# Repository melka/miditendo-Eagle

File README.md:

# miditendo

Eagle project for the miditendo, a USB midi controller in a SNES gamepad, using [v-usb](http://www.obdev.at/products/vusb/index.html)

Included is a small board for programming ATTiny45/85 via ICSP without soldering a header (piggyback).

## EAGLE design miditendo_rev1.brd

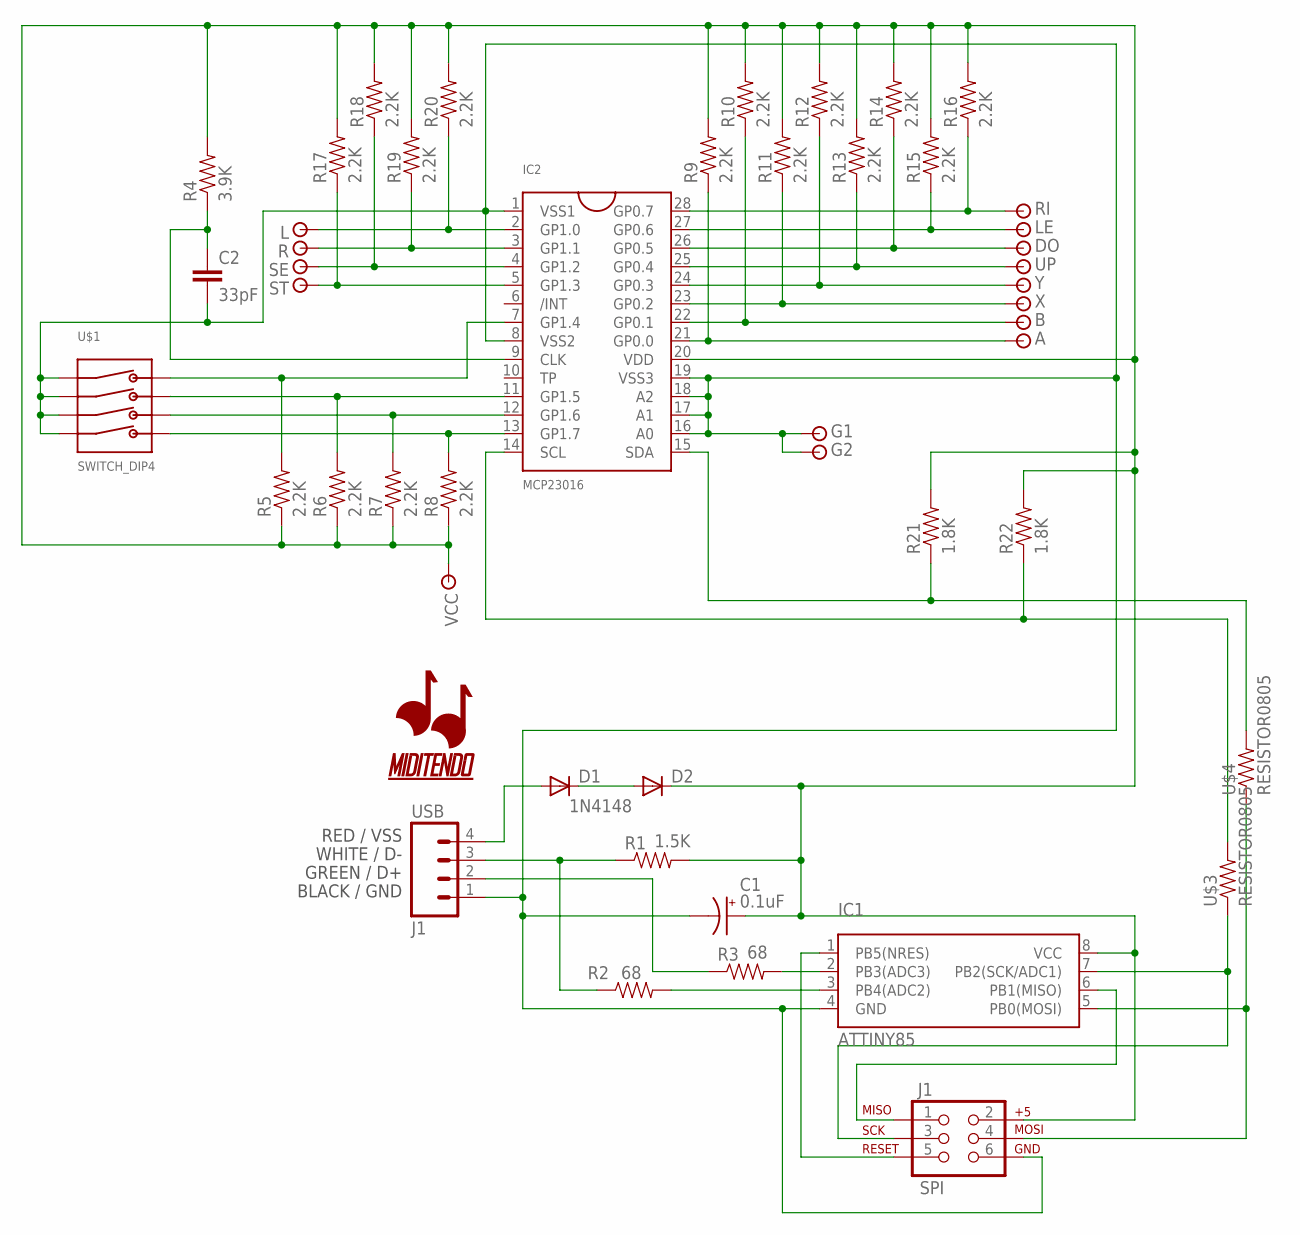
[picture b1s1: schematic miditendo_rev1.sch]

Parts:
A: WIRE_JOINT; THSOLDERPOINT
B: WIRE_JOINT; THSOLDERPOINT
C1: 0.1uF; POLCAP_2.54
C2: 33pF; 0805
D1: LL4148SOD-80C; SOD-80C
D2: 1N4148; SOD-80C
DO: WIRE_JOINT; THSOLDERPOINT
G1, G2: WIRE_JOINT; THSOLDERPOINT
IC1: ATTINY85; SOIC8-EIAJ
IC2: MCP23016; SOIC28
J1: SPI; 2X3-NS
L: WIRE_JOINT; THSOLDERPOINT
LE: WIRE_JOINT; THSOLDERPOINT
R: WIRE_JOINT; THSOLDERPOINT
R1: 1.5K; 0805
R2, R3: 68; 0805
R4: 3.9K; 0805
R5, R6, R7, R8, R9, R10, R11, R12, R13, R14, R15, R16, R17, R18, R19, R20: 2.2K; 0805
R21, R22: 1.8K; 0805
RI: WIRE_JOINT; THSOLDERPOINT
SE: WIRE_JOINT; THSOLDERPOINT
ST: WIRE_JOINT; THSOLDERPOINT
U$1: SWITCH_DIP4; SWITCH_4DIP
U$2: MIDITENDO
U$3, U$4: RESISTOR0805; 0805
UP: WIRE_JOINT; THSOLDERPOINT
USB: J1; 1X04_LONGPADS
VCC: WIRE_JOINT; THSOLDERPOINT
X: WIRE_JOINT; THSOLDERPOINT
Y: WIRE_JOINT; THSOLDERPOINT

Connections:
GND: C1.N (-), C2.2, G1.P$1, G2.P$1, IC1.4 (GND), IC2.1 (VSS1), IC2.8 (VSS2), IC2.16 (A0), IC2.17 (A1), IC2.18 (A2), IC2.19 (VSS3), J1.6, U$1.P$1, U$1.P$2, U$1.P$3, U$1.P$4, USB.1
unnamed: D1.PA (A), USB.4
unnamed: D1.PC (C), D2.PA (A)
unnamed: IC2.2 (GP1.0), L.P$1, R20.1
unnamed: IC2.15 (SDA), R21.1, U$4.2
unnamed: R3.1, USB.2
unnamed: IC2.14 (SCL), R22.1, U$3.2
unnamed: IC1.2 (PB3(ADC3)), R3.2
unnamed: IC1.3 (PB4(ADC2)), R2.2
unnamed: IC2.3 (GP1.1), R.P$1, R19.1
unnamed: R1.1, R2.1, USB.3
unnamed: IC2.4 (GP1.2), R18.1, SE.P$1
unnamed: IC2.5 (GP1.3), R17.1, ST.P$1
unnamed: IC2.28 (GP0.7), R16.1, RI.P$1
unnamed: IC2.27 (GP0.6), LE.P$1, R15.1
unnamed: DO.P$1, IC2.26 (GP0.5), R14.1
unnamed: IC2.25 (GP0.4), R13.1, UP.P$1
unnamed: IC2.24 (GP0.3), R12.1, Y.P$1
unnamed: IC2.23 (GP0.2), R11.1, X.P$1
unnamed: B.P$1, IC2.22 (GP0.1), R10.1
unnamed: A.P$1, IC2.21 (GP0.0), R9.1
unnamed: C2.1, IC2.9 (CLK), R4.1
unnamed: IC1.6 (PB1(MISO)), J1.1
unnamed: IC1.1 (PB5(NRES)), J1.5
unnamed: IC1.7 (PB2(SCK/ADC1)), J1.3, U$3.1
unnamed: IC1.5 (PB0(MOSI)), J1.4, U$4.1
unnamed: IC2.13 (GP1.7), R8.2, U$1.P$5
unnamed: IC2.12 (GP1.6), R7.2, U$1.P$6
unnamed: IC2.11 (GP1.5), R6.2, U$1.P$7
unnamed: IC2.7 (GP1.4), R5.2, U$1.P$8
VDD: C1.P (+), D2.PC (C), IC1.8 (VCC), IC2.20 (VDD), J1.2, R1.2, R4.2, R5.1, R6.1, R7.1, R8.1, R9.2, R10.2, R11.2, R12.2, R13.2, R14.2, R15.2, R16.2, R17.2, R18.2, R19.2, R20.2, R21.2, R22.2, VCC.P$1

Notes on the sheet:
RED / VSS
WHITE / D-
GREEN / D+
BLACK / GND

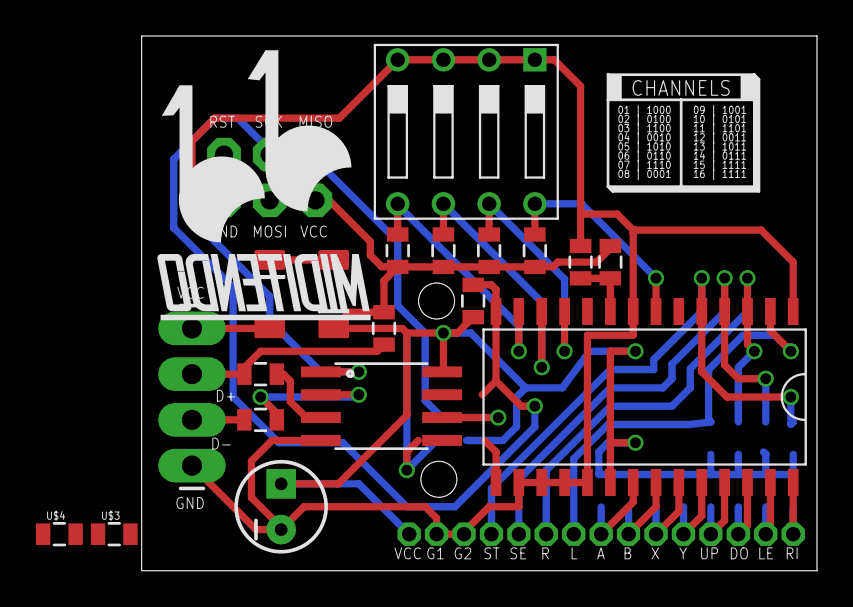
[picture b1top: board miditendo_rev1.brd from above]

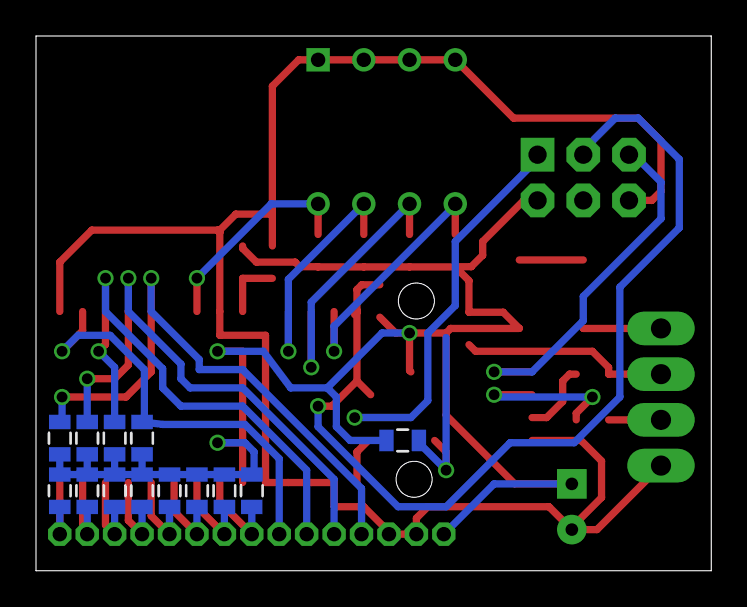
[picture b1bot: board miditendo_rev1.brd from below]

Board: 2 copper layers, 37.5 x 29.7 mm, 49 parts (14 on the bottom side), 31 nets.

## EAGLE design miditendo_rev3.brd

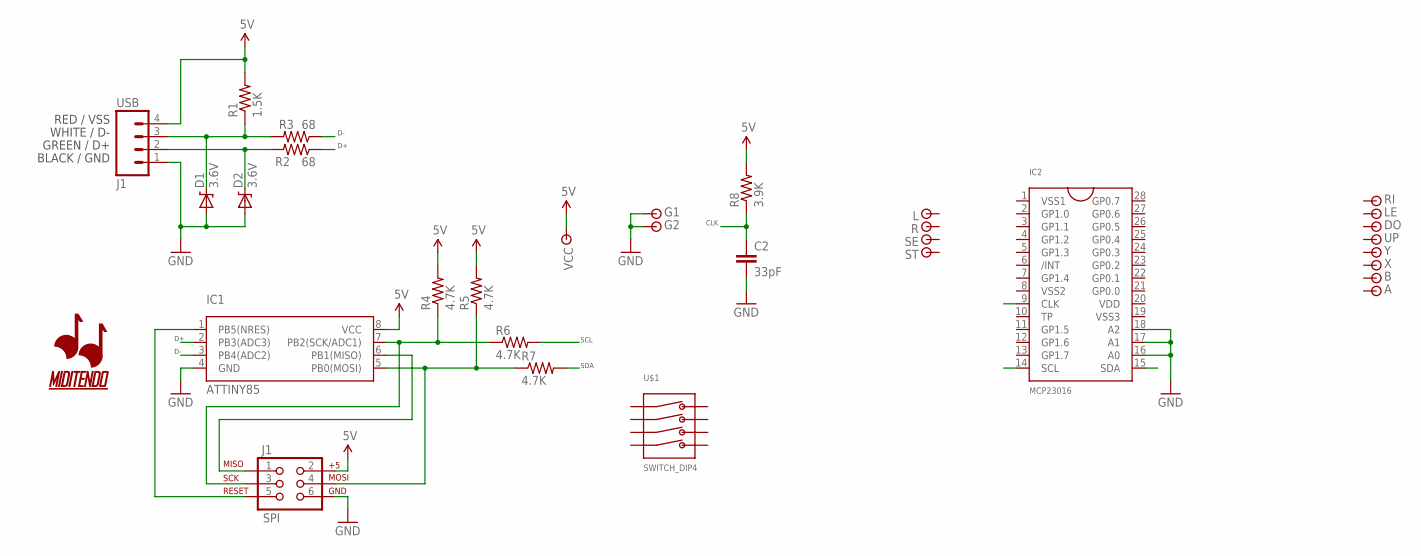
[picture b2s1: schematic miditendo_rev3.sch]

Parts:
A: WIRE_JOINT; THSOLDERPOINT
B: WIRE_JOINT; THSOLDERPOINT
C2: 33pF; 0805
D1, D2: 3.6V; DIODE-ZENER
DO: WIRE_JOINT; THSOLDERPOINT
G1, G2: WIRE_JOINT; THSOLDERPOINT
IC1: ATTINY85; SOIC8-EIAJ
IC2: MCP23016; SOIC28
J1: SPI; 2X3-NS
L: WIRE_JOINT; THSOLDERPOINT
LE: WIRE_JOINT; THSOLDERPOINT
R: WIRE_JOINT; THSOLDERPOINT
R1: 1.5K; 0805
R2, R3: 68; 0805
R4, R5, R6, R7: 4.7K; 0805
R8: 3.9K; 0805
RI: WIRE_JOINT; THSOLDERPOINT
SE: WIRE_JOINT; THSOLDERPOINT
ST: WIRE_JOINT; THSOLDERPOINT
U$1: SWITCH_DIP4; SWITCH_4DIP
U$2: MIDITENDO
UP: WIRE_JOINT; THSOLDERPOINT
USB: J1; 1X04_LONGPADS
VCC: WIRE_JOINT; THSOLDERPOINT
X: WIRE_JOINT; THSOLDERPOINT
Y: WIRE_JOINT; THSOLDERPOINT

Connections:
5V: IC1.8 (VCC), J1.2, R1.2, R4.2, R5.2, R8.2, USB.4, VCC.P$1
CLK: C2.1, IC2.9 (CLK), R8.1
D+: IC1.2 (PB3(ADC3)), R2.1
D-: IC1.3 (PB4(ADC2)), R3.1
GND: C2.2, D1.P$2 (A), D2.P$2 (A), G1.P$1, G2.P$1, IC1.4 (GND), IC2.16 (A0), IC2.17 (A1), IC2.18 (A2), J1.6, USB.1
MOSI: IC1.5 (PB0(MOSI)), J1.4, R5.1, R7.1
unnamed: D1.P$1 (C), R1.1, R3.2, USB.3
unnamed: IC1.1 (PB5(NRES)), J1.5
unnamed: D2.P$1 (C), R2.2, USB.2
unnamed: IC1.6 (PB1(MISO)), J1.1
SCK: IC1.7 (PB2(SCK/ADC1)), J1.3, R4.1, R6.1
SCL: IC2.14 (SCL), R6.2
SDA: IC2.15 (SDA), R7.2
VDD: IC2.20 (VDD)
VSS1: IC2.1 (VSS1)
VSS2: IC2.8 (VSS2)
VSS3: IC2.19 (VSS3)

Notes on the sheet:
RED / VSS
WHITE / D-
GREEN / D+
BLACK / GND
SCL
SDA
CLK

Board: 2 copper layers, 32 parts (0 on the bottom side), 13 nets, no tracks yet.

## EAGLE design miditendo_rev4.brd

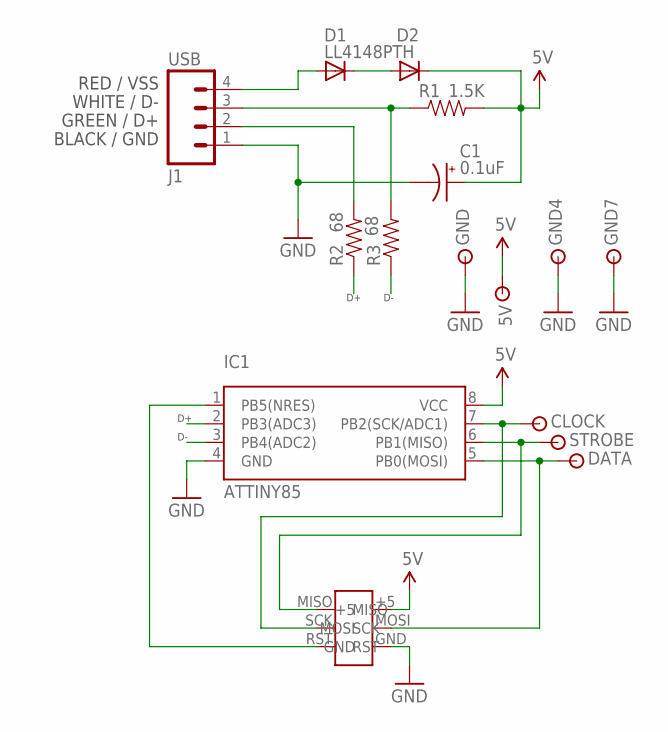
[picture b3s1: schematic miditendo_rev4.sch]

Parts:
5V: WIRE_JOINT; THSOLDERPOINT
C1: 0.1uF; POLCAP_2.54
CLOCK: WIRE_JOINT; THSOLDERPOINT
D1, D2: LL4148PTH; 1N4148-PTH
DATA: WIRE_JOINT; THSOLDERPOINT
GND, GND4, GND7: WIRE_JOINT; THSOLDERPOINT
IC1: ATTINY85; DIP8
R1: 1.5K; 0805
R2, R3: 68; 0805
STROBE: WIRE_JOINT; THSOLDERPOINT
U$1: ICSPSMD; ICSP_SMD
USB: J1; 1X04-SMD

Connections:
5V: 5V.P$1, C1.P (+), D2.C, IC1.8 (VCC), R1.2, U$1.+5
D+: IC1.2 (PB3(ADC3)), R2.1
D-: IC1.3 (PB4(ADC2)), R3.1
GND: C1.N (-), GND.P$1, GND4.P$1, GND7.P$1, IC1.4 (GND), U$1.GND, USB.1
MOSI: DATA.P$1, IC1.5 (PB0(MOSI)), U$1.MOSI
unnamed: D1.A, USB.4
unnamed: D1.C, D2.A
unnamed: IC1.6 (PB1(MISO)), STROBE.P$1, U$1.MISO
unnamed: CLOCK.P$1, IC1.7 (PB2(SCK/ADC1)), U$1.SCK
unnamed: R2.2, USB.2
unnamed: R1.1, R3.2, USB.3
unnamed: IC1.1 (PB5(NRES)), U$1.RST

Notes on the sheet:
RED / VSS
WHITE / D-
GREEN / D+
BLACK / GND

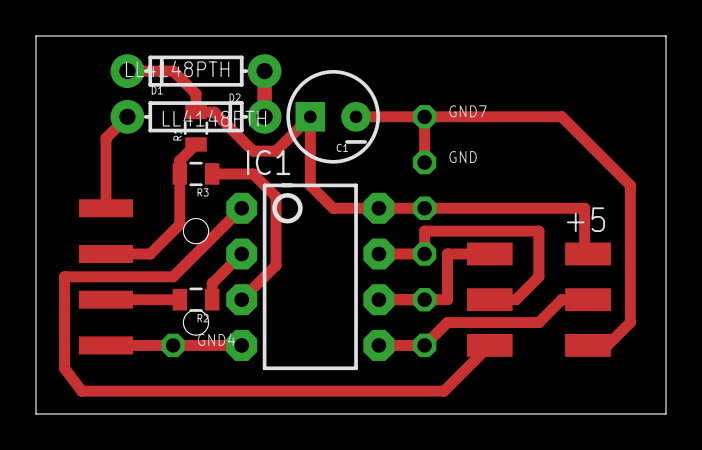
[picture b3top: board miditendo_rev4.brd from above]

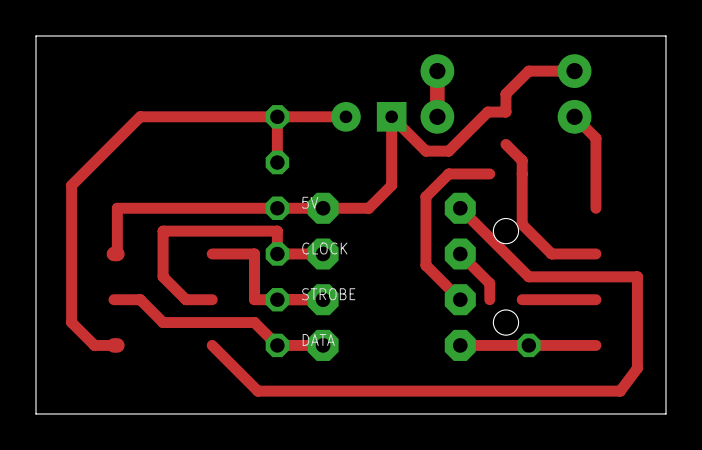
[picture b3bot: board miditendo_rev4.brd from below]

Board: 2 copper layers, 35.0 x 21.0 mm, 16 parts (4 on the bottom side), 12 nets.

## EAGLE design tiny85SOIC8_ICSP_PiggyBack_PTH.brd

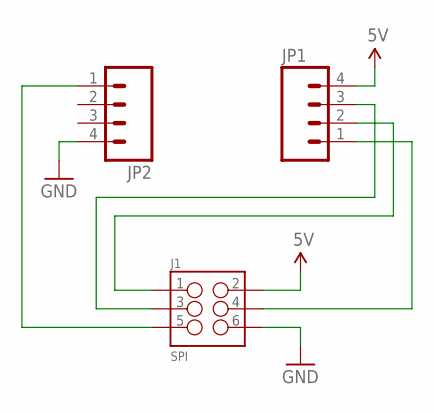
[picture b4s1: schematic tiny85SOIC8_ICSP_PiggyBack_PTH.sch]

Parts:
J1: SPI; 2X3-NS
JP1, JP2: M041.27MM; 1X04-1.27MM

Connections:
5V: J1.2, JP1.4
GND: J1.6, JP2.4
MISO: J1.1, JP1.2
MOSI: J1.4, JP1.1
RST: J1.5, JP2.1
SCK: J1.3, JP1.3

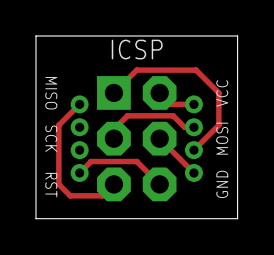
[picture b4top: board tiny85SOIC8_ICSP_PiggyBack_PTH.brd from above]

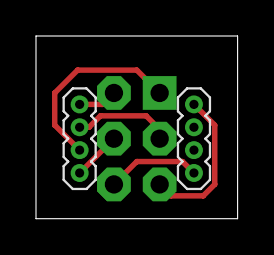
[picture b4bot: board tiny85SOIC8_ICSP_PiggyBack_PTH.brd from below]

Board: 4 copper layers, 11.2 x 10.2 mm, 3 parts (2 on the bottom side), 6 nets.

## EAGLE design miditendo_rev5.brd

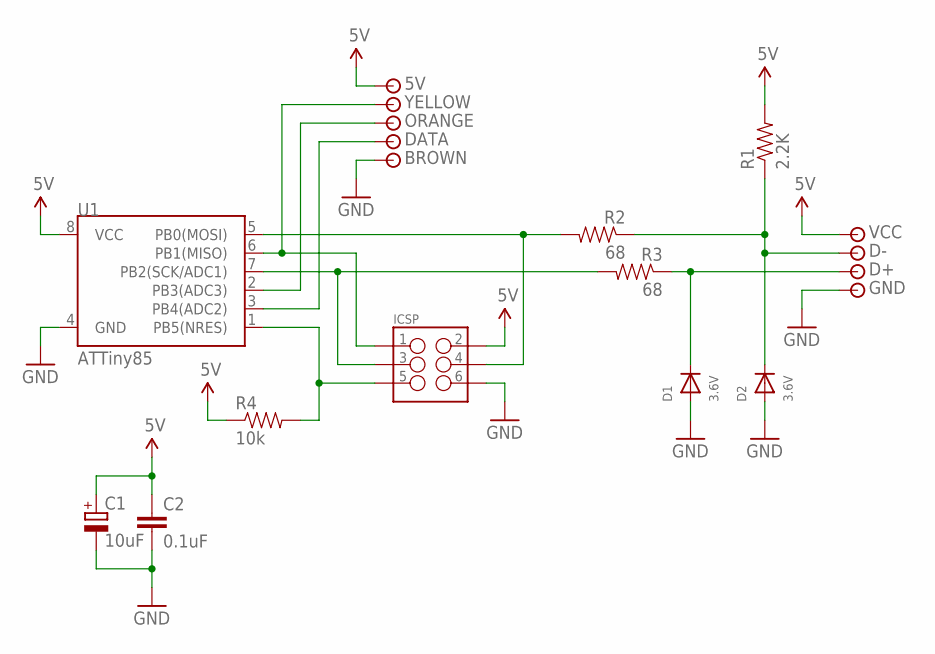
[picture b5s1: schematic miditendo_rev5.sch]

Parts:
5V: WIRE_JOINT; THSOLDERPOINT
BROWN: WIRE_JOINT; THSOLDERPOINT
C1: 10uF; PANASONIC_B
C2: 0.1uF; C0805
D1, D2: 3.6V; SOD-123
D+: WIRE_JOINT; THSOLDERPOINT
D-: WIRE_JOINT; THSOLDERPOINT
DATA: WIRE_JOINT; THSOLDERPOINT
GND: WIRE_JOINT; THSOLDERPOINT
ICSP: M03X2SMT; 2X3_SMT_POSTS
ORANGE: WIRE_JOINT; THSOLDERPOINT
R1: 2.2K; 0805
R2, R3: 68; 0805
R4: 10k; 0805
U1: ATTiny85; SO08-EIAJ
VCC: WIRE_JOINT; THSOLDERPOINT
YELLOW: WIRE_JOINT; THSOLDERPOINT

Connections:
5V: 5V.P$1, C1.+, C2.1, ICSP.2, R1.2, R4.1, U1.8 (VCC), VCC.P$1
GND: BROWN.P$1, C1.-, C2.2, D1.A, D2.A, GND.P$1, ICSP.6, U1.4 (GND)
unnamed: ICSP.4, R2.2, U1.5 (PB0(MOSI))
unnamed: ICSP.3, R3.2, U1.7 (PB2(SCK/ADC1))
unnamed: ICSP.1, U1.6 (PB1(MISO)), YELLOW.P$1
unnamed: ORANGE.P$1, U1.2 (PB3(ADC3))
unnamed: D2.C, D-.P$1, R1.1, R2.1
unnamed: DATA.P$1, U1.3 (PB4(ADC2))
unnamed: D1.C, D+.P$1, R3.1
unnamed: ICSP.5, R4.2, U1.1 (PB5(NRES))

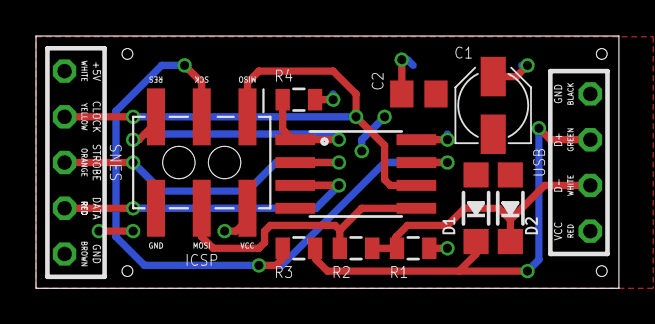
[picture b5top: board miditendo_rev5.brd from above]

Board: 2 copper layers, 32.4 x 14.0 mm, 20 parts (1 on the bottom side), 10 nets.

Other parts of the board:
U$1: MIDITENDO

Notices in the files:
parts and their libraries:
SparkFun: Licensing: CC v3.0 Share-Alike You are welcome to use this library for commercial purposes.
microbuilder: This work is placed in the public domain, and may be freely used for commercial and non-commercial work with the following conditions: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
